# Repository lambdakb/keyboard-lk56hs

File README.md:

# LK56HS 55% Staggered Hot-Swappable Keyboard

## Layout

[Keyboard Layout Editor](https://www.keyboard-layout-editor.com/##@_css=%3B&@_x:2.25&p=R1&a:7%3B&=%3Ci%20class%2F='mss%20mss-Unicode-Escape-3'%3E%3C%2F%2Fi%3E%0A%0A%0A%0A1U&=1%0A%0A%0A%0A1U&=2%0A%0A%0A%0A1U&=3%0A%0A%0A%0A1U&=4%0A%0A%0A%0A1U&=5%0A%0A%0A%0A1U&=6%0A%0A%0A%0A1U&=7%0A%0A%0A%0A1U&=8%0A%0A%0A%0A1U&=9%0A%0A%0A%0A1U&=0%0A%0A%0A%0A1U&_c=%23e377cc%3B&=-%0A%0A%0A%0A1U&=%2F=&_x:0.25&p=R4&w:2%3B&=%3Ci%20class%2F='kb%20kb-Unicode-BackSpace-DeleteLeft-Big'%3E%3C%2F%2Fi%3E%0A%0A%0A%0A2U%3B&@_x:2.25&c=%23cccccc&p=R2&w:1.5%3B&=%3Ci%20class%2F='kb%20kb-Tab-1'%3E%3C%2F%2Fi%3E%0A%0A%0A%0A1.5U&=Q%0A%0A%0A%0A1U&=W%0A%0A%0A%0A1U&=E%0A%0A%0A%0A1U&=R%0A%0A%0A%0A1U&=T%0A%0A%0A%0A1U&=Y%0A%0A%0A%0A1U&=U%0A%0A%0A%0A1U&=I%0A%0A%0A%0A1U&=O%0A%0A%0A%0A1U&=P%0A%0A%0A%0A1U&_w:1.5%3B&=%3Ci%20class%2F='kb%20kb-Unicode-BackSpace-DeleteLeft-Big'%3E%3C%2F%2Fi%3E%0A%0A%0A%0A1.50U%3B&@_x:2.25&p=R3&w:1.75%3B&=%3Ci%20class%2F='kb%20kb-Unicode-Lock-Closed-1'%3E%3C%2F%2Fi%3E%0A%0A%0A%0A1.75U&=A%0A%0A%0A%0A1U&=S%0A%0A%0A%0A1U&=D%0A%0A%0A%0A1U&_n:true%3B&=F%0A%0A%0A%0A1U&=G%0A%0A%0A%0A1U&=H%0A%0A%0A%0A1U&_n:true%3B&=J%0A%0A%0A%0A1U&=K%0A%0A%0A%0A1U&=L%0A%0A%0A%0A1U&_c=%2317aaff&p=R4&w:2.25%3B&=%3Ci%20class%2F='kb%20kb-Return-2'%3E%3C%2F%2Fi%3E%0A%0A%0A%0A2.25U&_x:0.25%3B&=%2F:%0A%0A%0A%0A1U&_w:1.25%3B&=%3Ci%20class%2F='kb%20kb-Return-2'%3E%3C%2F%2Fi%3E%0A%0A%0A%0A1.25U%3B&@_c=%2348bf00%3B&=%3Ci%20class%2F='kb%20kb-Arrows-Up-Circle-Filled'%3E%3C%2F%2Fi%3E%0A%0A%0A%0A1U&=%7C%0A%0A%0A%0A1U&_x:0.25&w:2%3B&=%3Ci%20class%2F='kb%20kb-Arrows-Up-Circle-Filled'%3E%3C%2F%2Fi%3E%0A%0A%0A%0A2U&_c=%23cccccc%3B&=Z%0A%0A%0A%0A1U&=X%0A%0A%0A%0A1U&=C%0A%0A%0A%0A1U&=V%0A%0A%0A%0A1U&=B%0A%0A%0A%0A1U&=N%0A%0A%0A%0A1U&=M%0A%0A%0A%0A1U&=%3C%0A%0A%0A%0A1U&=%3E%0A%0A%0A%0A1U&_c=%23b275ff%3B&=%3Ci%20class%2F='kb%20kb-Arrows-Up'%3E%3C%2F%2Fi%3E%0A%0A%0A%0A1U&=%3Ci%20class%2F='kb%20kb-Unicode-DeleteRight-Big'%3E%3C%2F%2Fi%3E%0A%0A%0A%0A1U&_x:0.25&w:2%3B&=%3Ci%20class%2F='kb%20kb-Arrows-Up-Circle-Filled'%3E%3C%2F%2Fi%3E%0A%0A%0A%0A2U%3B&@_c=%23cccccc&p=R2&w:2.25&d:true%3B&=MOD&_c=%23b56060&p=R4%3B&=%3Ci%20class%2F='mss%20mss-Unicode-Control-4'%3E%3C%2F%2Fi%3E%0A%0A%0A%0A1U&=%3Ci%20class%2F='kb%20kb-logo-linux-tux-ibm'%3E%3C%2F%2Fi%3E%0A%0A%0A%0A1U&=%3Ci%20class%2F='mss%20mss-Unicode-Option-3'%3E%3C%2F%2Fi%3E%0A%0A%0A%0A1U&=Fn%0A%0A%0A%0A1U&_c=%23ffbc36&p=SPACE&w:2.75%3B&=%0A%0A%0A%0A2.75U&_w:2.25%3B&=%0A%0A%0A%0A2.25U&_c=%2372ccc7%3B&=%3Ci%20class%2F='kb%20kb-Hamburger-Menu'%3E%3C%2F%2Fi%3E%0A%0A%0A%0A1U&_p=R2%3B&=%3Ci%20class%2F='kb%20kb-Arrows-Left'%3E%3C%2F%2Fi%3E%0A%0A%0A%0A1U&=%3Ci%20class%2F='kb%20kb-Arrows-Down'%3E%3C%2F%2Fi%3E%0A%0A%0A%0A1U&=%3Ci%20class%2F='kb%20kb-Arrows-Right'%3E%3C%2F%2Fi%3E%0A%0A%0A%0A1U&_c=%23cccccc&w:2.5&d:true%3B&=ARROW%3B&@_y:0.25&w:2.25&d:true%3B&=STD&_c=%23b56060&p=R4&w:1.5%3B&=%3Ci%20class%2F='mss%20mss-Unicode-Control-4'%3E%3C%2F%2Fi%3E%0A%0A%0A%0A1.5U&=%3Ci%20class%2F='kb%20kb-logo-linux-tux-ibm'%3E%3C%2F%2Fi%3E%0A%0A%0A%0A1U&_w:1.5%3B&=%3Ci%20class%2F='mss%20mss-Unicode-Option-3'%3E%3C%2F%2Fi%3E%0A%0A%0A%0A1.5U&_c=%23ffbc36&p=SPACE&w:2.75%3B&=%0A%0A%0A%0A2.75U&_w:2.25%3B&=%0A%0A%0A%0A2.25U&_c=%2372ccc7&p=R2&w:1.5%3B&=%3Ci%20class%2F='mss%20mss-Unicode-Option-3'%3E%3C%2F%2Fi%3E%0A%0A%0A%0A1.5U&_p=R4%3B&=%3Ci%20class%2F='kb%20kb-logo-linux-tux-ibm'%3E%3C%2F%2Fi%3E%0A%0A%0A%0A1U&_p=R2&w:1.5%3B&=%3Ci%20class%2F='mss%20mss-Unicode-Control-4'%3E%3C%2F%2Fi%3E%0A%0A%0A%0A1.5U&_c=%23cccccc&w:2.5&d:true%3B&=STD%3B&@_w:2.25&d:true%3B&=WKL&_c=%23b56060&p=R4&w:1.5%3B&=%3Ci%20class%2F='mss%20mss-Unicode-Control-4'%3E%3C%2F%2Fi%3E%0A%0A%0A%0A1.5U&_x:1&w:1.5%3B&=%3Ci%20class%2F='mss%20mss-Unicode-Option-3'%3E%3C%2F%2Fi%3E%0A%0A%0A%0A1.5U&_c=%23ffbc36&p=SPACE&w:2.75%3B&=%0A%0A%0A%0A2.75U&_w:2.25%3B&=%0A%0A%0A%0A2.25U&_c=%2372ccc7&p=R2&w:1.5%3B&=%3Ci%20class%2F='mss%20mss-Unicode-Option-3'%3E%3C%2F%2Fi%3E%0A%0A%0A%0A1.5U&_x:1&w:1.5%3B&=%3Ci%20class%2F='mss%20mss-Unicode-Control-4'%3E%3C%2F%2Fi%3E%0A%0A%0A%0A1.5U&_c=%23cccccc&w:2.5&d:true%3B&=WKL%3B&@_w:2.25&d:true%3B&=HHKB&_x:1.5&c=%23b56060&p=R4%3B&=%3Ci%20class%2F='kb%20kb-logo-linux-tux-ibm'%3E%3C%2F%2Fi%3E%0A%0A%0A%0A1U&_w:1.5%3B&=%3Ci%20class%2F='mss%20mss-Unicode-Option-3'%3E%3C%2F%2Fi%3E%0A%0A%0A%0A1.5U&_c=%23ffbc36&p=SPACE&w:2.75%3B&=%0A%0A%0A%0A2.75U&_w:2.25%3B&=%0A%0A%0A%0A2.25U&_c=%2372ccc7&p=R2&w:1.5%3B&=%3Ci%20class%2F='mss%20mss-Unicode-Option-3'%3E%3C%2F%2Fi%3E%0A%0A%0A%0A1.5U&_p=R4%3B&=%3Ci%20class%2F='kb%20kb-logo-linux-tux-ibm'%3E%3C%2F%2Fi%3E%0A%0A%0A%0A1U&_x:1.5&c=%23cccccc&p=R2&w:2.5&d:true%3B&=HHKB%3B&@_w:2.25&d:true%3B&=BIG&_c=%23b56060&p=R4&w:1.5%3B&=%3Ci%20class%2F='mss%20mss-Unicode-Control-4'%3E%3C%2F%2Fi%3E%0A%0A%0A%0A1.5U&=%3Ci%20class%2F='kb%20kb-logo-linux-tux-ibm'%3E%3C%2F%2Fi%3E%0A%0A%0A%0A1U&_w:1.5%3B&=%3Ci%20class%2F='mss%20mss-Unicode-Option-3'%3E%3C%2F%2Fi%3E%0A%0A%0A%0A1.5U&_c=%23ffbc36&p=SPACE&w:6%3B&=%0A%0A%0A%0A6U&_c=%2372ccc7&p=R2%3B&=%3Ci%20class%2F='mss%20mss-Unicode-Option-3'%3E%3C%2F%2Fi%3E%0A%0A%0A%0A1U&=%3Ci%20class%2F='kb%20kb-logo-linux-tux-ibm'%3E%3C%2F%2Fi%3E%0A%0A%0A%0A1U&=%3Ci%20class%2F='mss%20mss-Unicode-Control-4'%3E%3C%2F%2Fi%3E%0A%0A%0A%0A1U&_c=%23cccccc&w:2.5&d:true%3B&=BIG)

## PCB

|          PCB (Front)          |         PCB (Back)          |
| :---------------------------: | :-------------------------: |
| [![PCB Front]][PCB Front PNG] | [![PCB Back]][PCB Back PNG] |

[PCB Front]: output/pcb/img/lk56hs-pcb-top.svg
[PCB Front PNG]: output/pcb/img/lk56hs-pcb-top.png
[PCB Back]: output/pcb/img/lk56hs-pcb-bottom.svg
[PCB Back PNG]: output/pcb/img/lk56hs-pcb-bottom.png

The PCB has been designed in [KiCad EDA 9.0](https://www.kicad.org/) using the [`kicad-lkbd`](https://github.com/lambdakb/kicad-lkbd) libraries and [`kbplacer`](https://github.com/adamws/kicad-kbplacer).

You can preview the project files using [KiCanvas](https://kicanvas.org/?github=https%3A%2F%2Fgithub.com%2Flambdakb%2Fkeyboard-lk56hs%2Fblob%2Fmain%2Fpcb%2Flk56hs-pcb.kicad_pro) directly in your browser and download the latest fabrication files for JLCPCB from the [latest release](https://github.com/lambdakb/keyboard-lk56hs/releases/latest/).

The exported schematic is also available under [`output/schematics`](output/schematics/).

### PCB Order

| Parameters                       | Value                  |
| -------------------------------- | ---------------------- |
| Base Material                    | FR4                    |
| Layers                           | 2                      |
| Dimensions                       | 247.65 × 95.25 mm      |
| PCB Thickness                    | 1.6 mm                 |
| PCB Color                        | Blue                   |
| Silkscreen                       | White                  |
| Surface Finish [^surface-finish] | Lead Free HASL or ENIG |
| Copper Weight                    | 1 oz                   |
| Via Covering                     | Tented                 |
| Min Via Hole Size                | 0.3 mm                 |
| Board Outline Tolerance          | ± 0.2 mm               |

[^surface-finish]: The "HASL (with lead)" option is extremely discouraged due to the risk of lead poisoning. We strongly recommend paying the premium for the "Lead Free HASL" option.

## Cases

### FR4

|          Plate (Top)          |           Plate (Bottom)            |
| :---------------------------: | :---------------------------------: |
| [![Plate Top]][Plate Top PNG] | [![Plate Bottom]][Plate Bottom PNG] |

[Plate Top]: output/plate/img/lk56hs-plate-top.svg
[Plate Top PNG]: output/plate/img/lk56hs-plate-top.png
[Plate Bottom]: output/plate/img/lk56hs-plate-bottom.svg
[Plate Bottom PNG]: output/plate/img/lk56hs-plate-bottom.png

The plate has also been designed in [KiCad EDA 9.0](https://www.kicad.org/) using the [`kicad-lkbd`](https://github.com/lambdakb/kicad-lkbd) libraries.

It is reversible, so you can choose to either have a wave pattern design shown or just a plain PCB plate. It can be used alongside another Keyboard PCB to create a full case by stacking:

- Plate PCB (any direction)
- Assemble Keyboard PCB
- Reversed Unpopulated Keyboard PCB

Use the same parameters present in [PCB Order](./README.md#pcb-order) to order the plate and bottom PCB, you can find the fabrication files in [`output/plate/fabrication/jlcpcb`](output/plate/fabrication/jlcpcb/).

Be careful, JLCPCB may charge an extra fee for this PCB because it has "too many holes". You may want to prefer 3D printing a full case instead.

If you prefer to fabricate it by any other mean (such as laser cut acrylic), you can download their board outlines as `DXF` in [`output/plate/dxf`](output/plate/dxf).

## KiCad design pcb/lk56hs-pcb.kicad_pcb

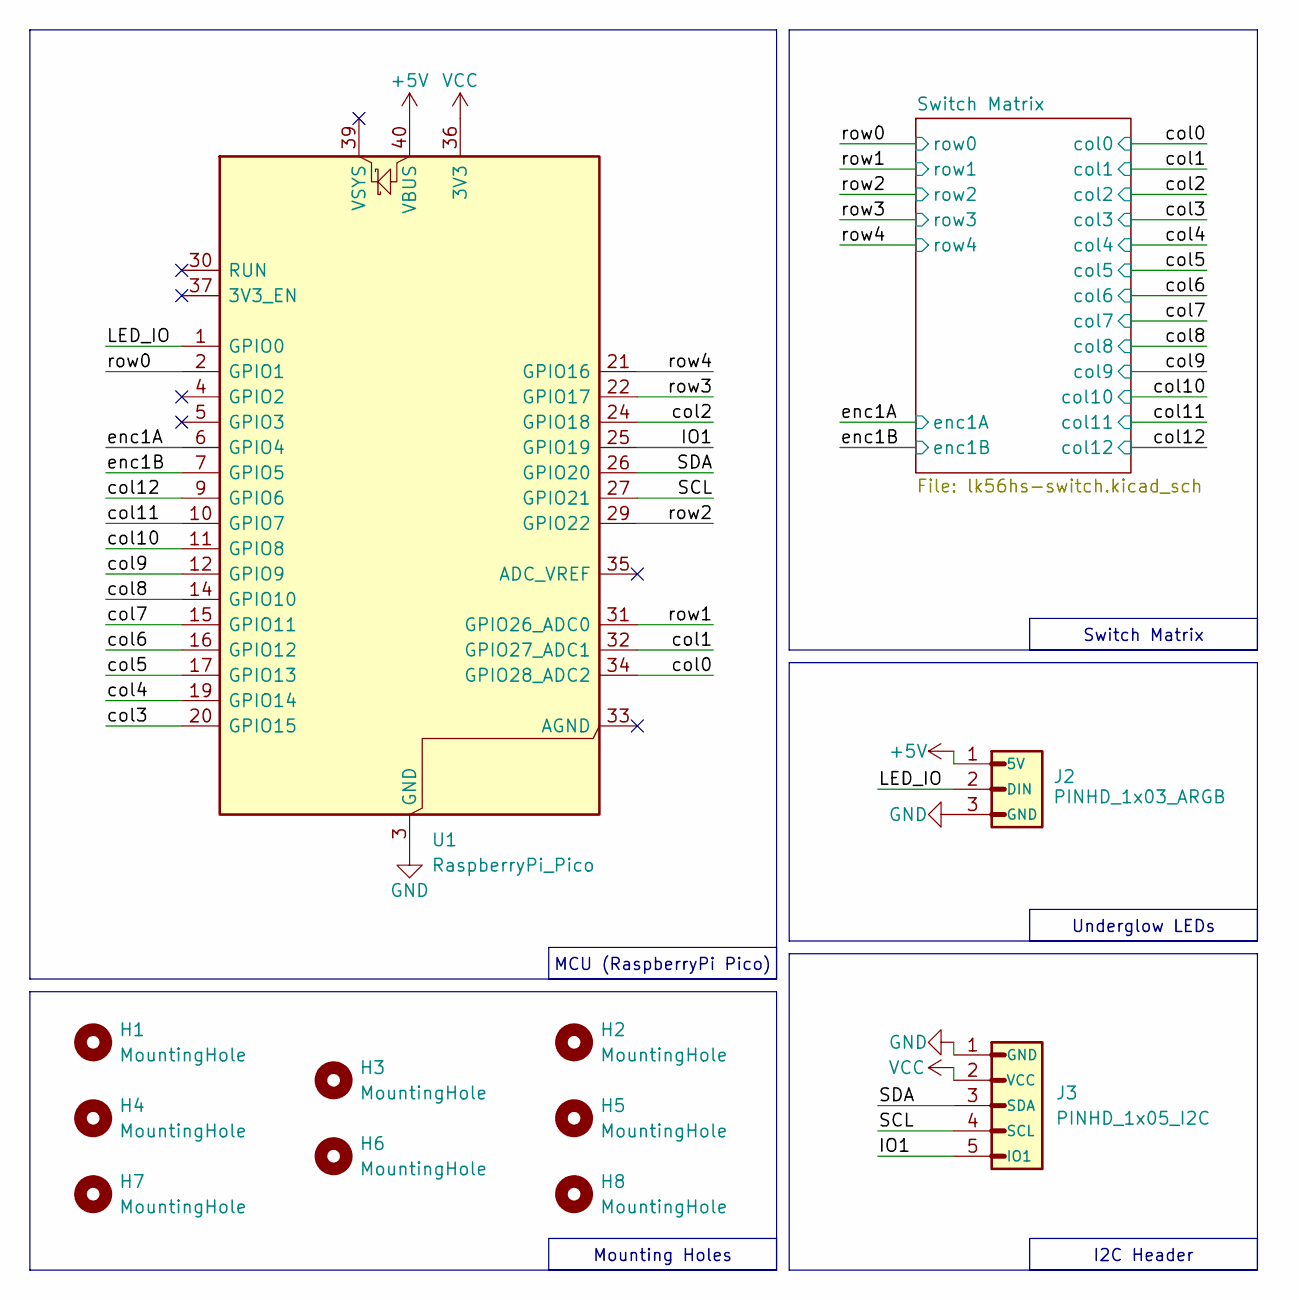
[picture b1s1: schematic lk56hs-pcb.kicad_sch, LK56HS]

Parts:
H1, H2, H3, H4, H5, H6, H7, H8: MountingHole; MountingHole_M2_NoPad
J2: PINHD_1x03_ARGB; PinHeader_1x03_THT_P2.54mm_nSilk
J3: PINHD_1x05_I2C; PinHeader_1x05_THT_P2.54mm_nSilk
U1: RaspberryPi_Pico; MCU_RaspberryPi_Pico_THT

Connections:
+5V: J2.1 (5V), U1.40 (VBUS)
/IO1: J3.5 (IO1), U1.25 (GPIO19)
/LED_IO: J2.2 (DIN), U1.1 (GPIO0)
/SCL: J3.4 (SCL), U1.27 (GPIO21)
/SDA: J3.3 (SDA), U1.26 (GPIO20)
/col0: U1.34 (GPIO28_ADC2); also elsewhere on the board
/col1: U1.32 (GPIO27_ADC1); also elsewhere on the board
/col2: U1.24 (GPIO18); also elsewhere on the board
/col3: U1.20 (GPIO15); also elsewhere on the board
/col4: U1.19 (GPIO14); also elsewhere on the board
/col5: U1.17 (GPIO13); also elsewhere on the board
/col6: U1.16 (GPIO12); also elsewhere on the board
/col7: U1.15 (GPIO11); also elsewhere on the board
/col8: U1.14 (GPIO10); also elsewhere on the board
/col9: U1.12 (GPIO9); also elsewhere on the board
/col10: U1.11 (GPIO8); also elsewhere on the board
/col11: U1.10 (GPIO7); also elsewhere on the board
/col12: U1.9 (GPIO6); also elsewhere on the board
/enc1A: U1.6 (GPIO4); also elsewhere on the board
/enc1B: U1.7 (GPIO5); also elsewhere on the board
/row0: U1.2 (GPIO1); also elsewhere on the board
/row1: U1.31 (GPIO26_ADC0); also elsewhere on the board
/row2: U1.29 (GPIO22); also elsewhere on the board
/row3: U1.22 (GPIO17); also elsewhere on the board
/row4: U1.21 (GPIO16); also elsewhere on the board
GND: J2.3 (GND), J3.1 (GND), U1.3 (GND), U1.8 (GND), U1.13 (GND), U1.18 (GND), U1.23 (GND), U1.28 (GND), U1.38 (GND); also elsewhere on the board
VCC: J3.2 (VCC), U1.36 (3V3)

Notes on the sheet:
Mounting Holes
Switch Matrix
MCU (RaspberryPi Pico)
Underglow LEDs
I2C Header

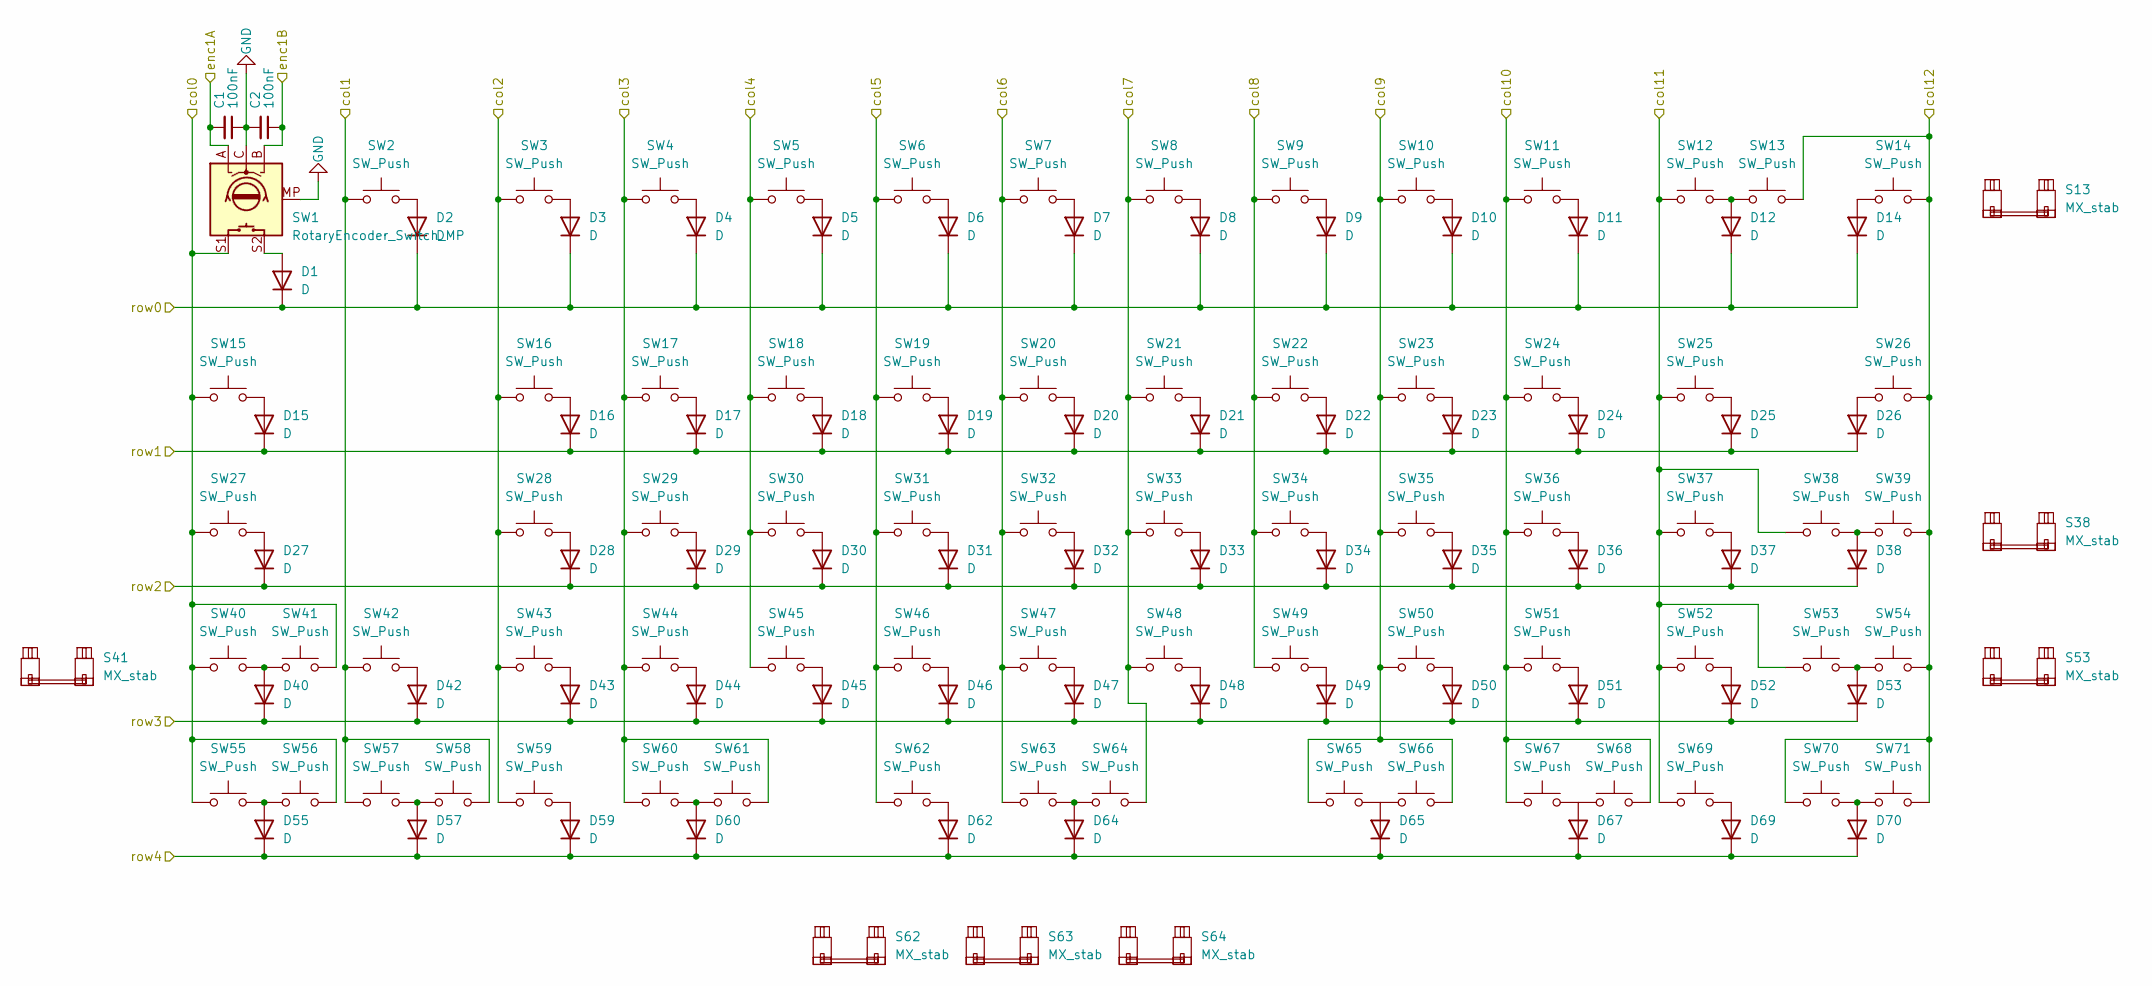
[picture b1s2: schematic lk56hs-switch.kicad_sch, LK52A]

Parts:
C1, C2: 100nF; Capacitor_SMD_1206_inSilk; LCSC C24497
D1, D2, D3, D4, D5, D6, D7, D8, D9, D10, D11, D12, D14, D15, D16, D17, D18, D19, D20, D21, D22, D23, D24, D25, D26, D27, D28, D29, D30, D31, D32, D33, D34, D35, D36, D37, D38, D40, D42, D43, D44, D45, D46, D47, D48, D49, D50, D51, D52, D53, D55, D57, D59, D60, D62, D64, D65, D67, D69, D70: D; Diode_SMD_SOD-123_inSilk; JLC SOD-123
S13, S38, S41, S53, S62, S64: MX_stab; Stabilizer_MX_2U
S63: MX_stab; Stabilizer_MX_6U
SW1: RotaryEncoder_Switch_MP; SW_MX_EC11_HotSwap_nSilk; JLC SMD,14.5x5.9mm
SW2, SW3, SW4, SW5, SW6, SW7, SW8, SW9, SW10, SW11, SW12, SW13, SW14, SW15, SW16, SW17, SW18, SW19, SW20, SW21, SW22, SW23, SW24, SW25, SW26, SW27, SW28, SW29, SW30, SW31, SW32, SW33, SW34, SW35, SW36, SW37, SW38, SW39, SW40, SW41, SW42, SW43, SW44, SW45, SW46, SW47, SW48, SW49, SW50, SW51, SW52, SW53, SW54, SW55, SW56, SW57, SW58, SW59, SW60, SW61, SW62, SW63, SW64, SW65, SW66, SW67, SW68, SW69, SW70, SW71: SW_Push; SW_MX_HotSwap_nSilk; JLC SMD,14.5x5.9mm

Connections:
/col0: SW1.S1, SW15.1, SW27.1, SW40.1, SW41.1, SW55.2, SW56.1; also elsewhere on the board
/col1: SW2.1, SW42.1, SW57.2, SW58.2; also elsewhere on the board
/col2: SW3.1, SW16.1, SW28.1, SW43.1, SW59.2; also elsewhere on the board
/col3: SW4.1, SW17.1, SW29.1, SW44.1, SW60.2, SW61.1; also elsewhere on the board
/col4: SW5.1, SW18.1, SW30.1, SW45.1; also elsewhere on the board
/col5: SW6.1, SW19.1, SW31.1, SW46.1, SW62.1; also elsewhere on the board
/col6: SW7.1, SW20.1, SW32.1, SW47.1, SW63.1; also elsewhere on the board
/col7: SW8.1, SW21.1, SW33.1, SW48.1, SW64.1; also elsewhere on the board
/col8: SW9.1, SW22.1, SW34.1, SW49.1; also elsewhere on the board
/col9: SW10.1, SW23.1, SW35.1, SW50.1, SW65.2, SW66.1; also elsewhere on the board
/col10: SW11.1, SW24.1, SW36.1, SW51.1, SW67.1, SW68.1; also elsewhere on the board
/col11: SW12.2, SW25.2, SW37.2, SW38.2, SW52.2, SW53.2, SW69.1; also elsewhere on the board
/col12: SW13.2, SW14.2, SW26.1, SW39.1, SW54.1, SW70.2, SW71.1; also elsewhere on the board
/enc1A: C1.2, SW1.A; also elsewhere on the board
/enc1B: C2.1, SW1.B; also elsewhere on the board
/row0: D1.1 (K), D2.1 (K), D3.1 (K), D4.1 (K), D5.1 (K), D6.1 (K), D7.1 (K), D8.1 (K), D9.1 (K), D10.1 (K), D11.1 (K), D12.1 (K), D14.1 (K); also elsewhere on the board
/row1: D15.1 (K), D16.1 (K), D17.1 (K), D18.1 (K), D19.1 (K), D20.1 (K), D21.1 (K), D22.1 (K), D23.1 (K), D24.1 (K), D25.1 (K), D26.1 (K); also elsewhere on the board
/row2: D27.1 (K), D28.1 (K), D29.1 (K), D30.1 (K), D31.1 (K), D32.1 (K), D33.1 (K), D34.1 (K), D35.1 (K), D36.1 (K), D37.1 (K), D38.1 (K); also elsewhere on the board
/row3: D40.1 (K), D42.1 (K), D43.1 (K), D44.1 (K), D45.1 (K), D46.1 (K), D47.1 (K), D48.1 (K), D49.1 (K), D50.1 (K), D51.1 (K), D52.1 (K), D53.1 (K); also elsewhere on the board
/row4: D55.1 (K), D57.1 (K), D59.1 (K), D60.1 (K), D62.1 (K), D64.1 (K), D65.1 (K), D67.1 (K), D69.1 (K), D70.1 (K); also elsewhere on the board
GND: C1.1, C2.2, SW1.C, SW1.MP; also elsewhere on the board
unnamed: D1.2 (A), SW1.S2
unnamed: D2.2 (A), SW2.2
unnamed: D3.2 (A), SW3.2
unnamed: D4.2 (A), SW4.2
unnamed: D5.2 (A), SW5.2
unnamed: D6.2 (A), SW6.2
unnamed: D7.2 (A), SW7.2
unnamed: D8.2 (A), SW8.2
unnamed: D9.2 (A), SW9.2
unnamed: D10.2 (A), SW10.2
unnamed: D11.2 (A), SW11.2
unnamed: D12.2 (A), SW12.1, SW13.1
unnamed: D14.2 (A), SW14.1
unnamed: D15.2 (A), SW15.2
unnamed: D16.2 (A), SW16.2
unnamed: D17.2 (A), SW17.2
unnamed: D18.2 (A), SW18.2
unnamed: D19.2 (A), SW19.2
unnamed: D20.2 (A), SW20.2
unnamed: D21.2 (A), SW21.2
unnamed: D22.2 (A), SW22.2
unnamed: D23.2 (A), SW23.2
unnamed: D24.2 (A), SW24.2
unnamed: D25.2 (A), SW25.1
unnamed: D26.2 (A), SW26.2
unnamed: D27.2 (A), SW27.2
unnamed: D28.2 (A), SW28.2
unnamed: D29.2 (A), SW29.2
unnamed: D30.2 (A), SW30.2
unnamed: D31.2 (A), SW31.2
unnamed: D32.2 (A), SW32.2
unnamed: D33.2 (A), SW33.2
unnamed: D34.2 (A), SW34.2
unnamed: D35.2 (A), SW35.2
unnamed: D36.2 (A), SW36.2
unnamed: D37.2 (A), SW37.1
unnamed: D38.2 (A), SW38.1, SW39.2
unnamed: D40.2 (A), SW40.2, SW41.2
unnamed: D42.2 (A), SW42.2
unnamed: D43.2 (A), SW43.2
unnamed: D44.2 (A), SW44.2
unnamed: D45.2 (A), SW45.2
unnamed: D46.2 (A), SW46.2
unnamed: D47.2 (A), SW47.2
unnamed: D48.2 (A), SW48.2
unnamed: D49.2 (A), SW49.2
unnamed: D50.2 (A), SW50.2
unnamed: D51.2 (A), SW51.2
unnamed: D52.2 (A), SW52.1
unnamed: D53.2 (A), SW53.1, SW54.2
unnamed: D55.2 (A), SW55.1, SW56.2
unnamed: D57.2 (A), SW57.1, SW58.1
unnamed: D59.2 (A), SW59.1
unnamed: D60.2 (A), SW60.1, SW61.2
unnamed: D62.2 (A), SW62.2
unnamed: D64.2 (A), SW63.2, SW64.2
unnamed: D65.2 (A), SW65.1, SW66.2
unnamed: D67.2 (A), SW67.2, SW68.2
unnamed: D69.2 (A), SW69.2
unnamed: D70.2 (A), SW70.1, SW71.2

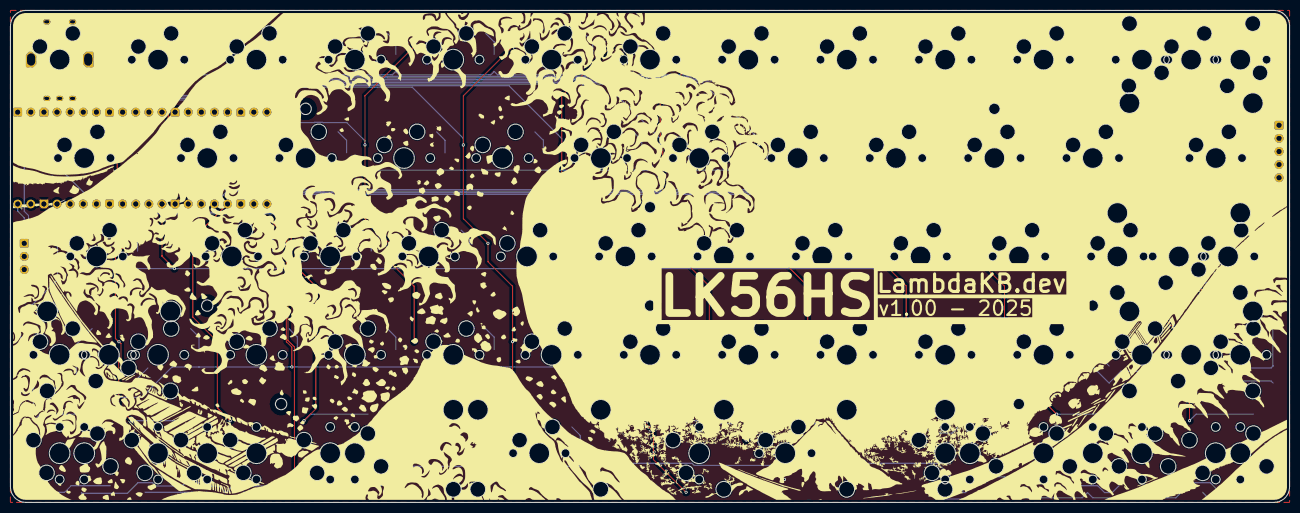
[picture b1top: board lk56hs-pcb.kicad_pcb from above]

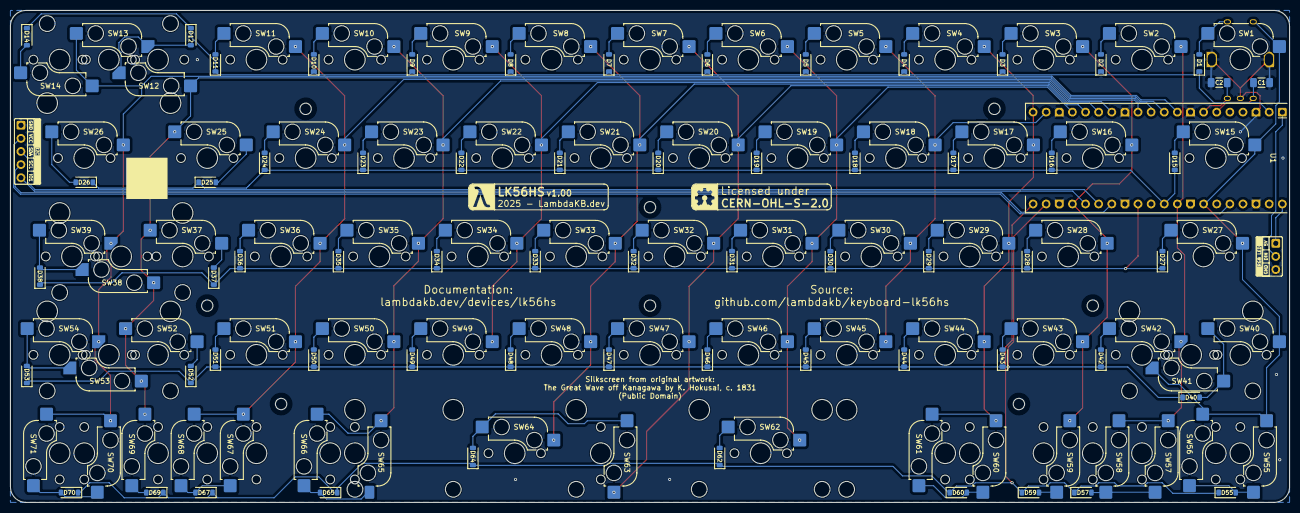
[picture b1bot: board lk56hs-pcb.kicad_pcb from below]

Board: 2 copper layers, 247.7 x 95.2 mm, 152 parts (137 on the bottom side), 87 nets.

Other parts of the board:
FAB1: JLCPCB_2DBarcode_8x8mm

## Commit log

2025-05-20 Add LK56HS PCB prototype
2025-05-20 Add output
2025-05-20 Update silkscreen
2025-05-20 Add simple plate
2025-05-20 Update stabilizers
2025-05-26 Make plate reversible and add graphics
2025-05-26 Fix CPL output

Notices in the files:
README.md:
License: CERN-OHL-S-2.0
pcb/lk56hs-pcb.kicad_pcb:
(Public Domain)
CERN-OHL-S-2.0
Licensed under
